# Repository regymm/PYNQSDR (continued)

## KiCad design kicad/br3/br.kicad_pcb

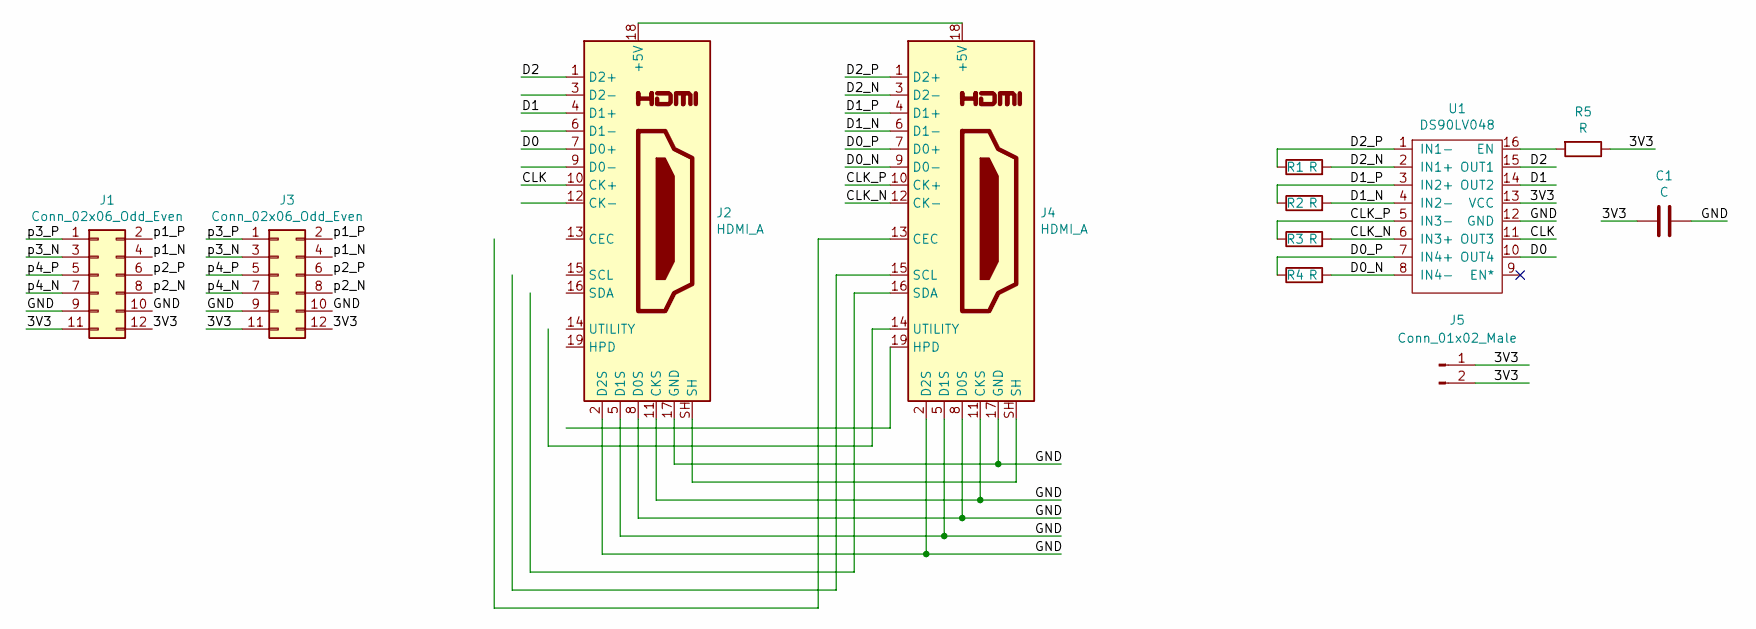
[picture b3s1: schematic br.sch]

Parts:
C1: C; C_0603_1608Metric_Pad1.08x0.95mm_HandSolder
J1, J3: Conn_02x06_Odd_Even; PinHeader_2x06_P2.54mm_Vertical
J2, J4: HDMI_A; HDMI_A_Kycon_KDMIX-SL1-NS-WS-B15_VerticalRightAngle
J5: Conn_01x02_Male; PinHeader_1x02_P2.54mm_Vertical
R1, R2, R3, R4, R5: R; R_0402_1005Metric_Pad0.72x0.64mm_HandSolder
U1: DS90LV048; SOIC-16_3.9x9.9mm_P1.27mm

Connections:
/3V3: C1.1, J1.11, J1.12, J3.11, J3.12, J5.1, J5.2, R5.1, U1.13 (VCC)
/CLK: J2.10 (CK+), U1.11 (OUT3)
/CLK_N: J4.12 (CK-), R3.2, U1.6 (IN3+)
/CLK_P: J4.10 (CK+), R3.1, U1.5 (IN3-)
/D0: J2.7 (D0+), U1.10 (OUT4)
/D0_N: J4.9 (D0-), R4.2, U1.8 (IN4-)
/D0_P: J4.7 (D0+), R4.1, U1.7 (IN4+)
/D1: J2.4 (D1+), U1.14 (OUT2)
/D1_N: J4.6 (D1-), R2.2, U1.4 (IN2-)
/D1_P: J4.4 (D1+), R2.1, U1.3 (IN2+)
/D2: J2.1 (D2+), U1.15 (OUT1)
/D2_N: J4.3 (D2-), R1.2, U1.2 (IN1+)
/D2_P: J4.1 (D2+), R1.1, U1.1 (IN1-)
/GND: C1.2, J1.9, J1.10, J2.2 (D2S), J2.5 (D1S), J2.8 (D0S), J2.11 (CKS), J2.17 (GND), J3.9, J3.10, J4.2 (D2S), J4.5 (D1S), J4.8 (D0S), J4.11 (CKS), J4.17 (GND), U1.12 (GND)
/p1_N: J1.4, J3.4
/p1_P: J1.2, J3.2
/p2_N: J1.8, J3.8
/p2_P: J1.6, J3.6
/p3_N: J1.3, J3.3
/p3_P: J1.1, J3.1
/p4_N: J1.7, J3.7
/p4_P: J1.5, J3.5
unnamed: J2.18 (+5V), J4.18 (+5V)
unnamed: J2.SH, J4.SH
unnamed: R5.2, U1.16 (EN)

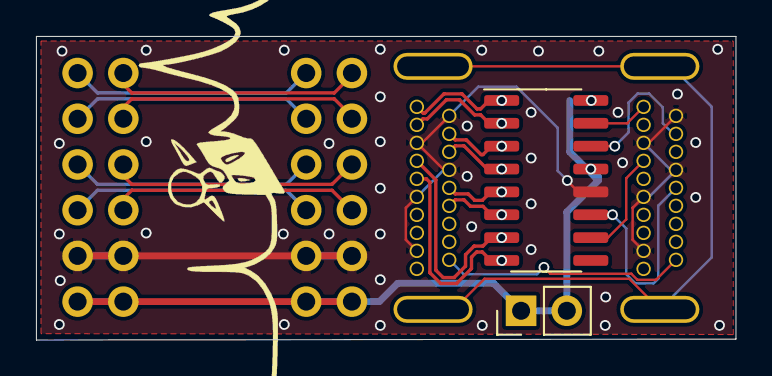
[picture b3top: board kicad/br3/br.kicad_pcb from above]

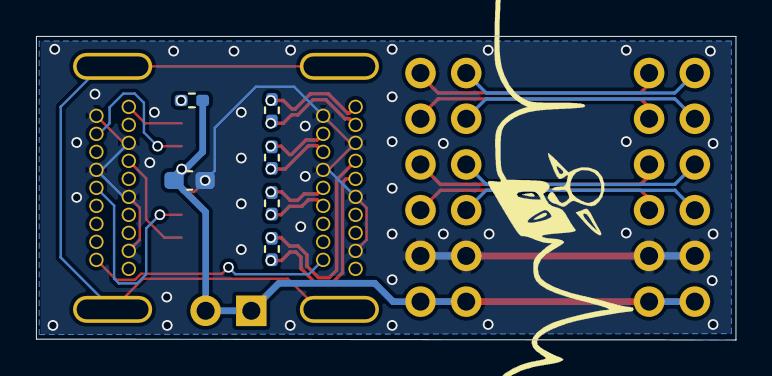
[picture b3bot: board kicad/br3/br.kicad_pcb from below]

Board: 2 copper layers, 38.9 x 16.9 mm, 12 parts (6 on the bottom side), 25 nets.

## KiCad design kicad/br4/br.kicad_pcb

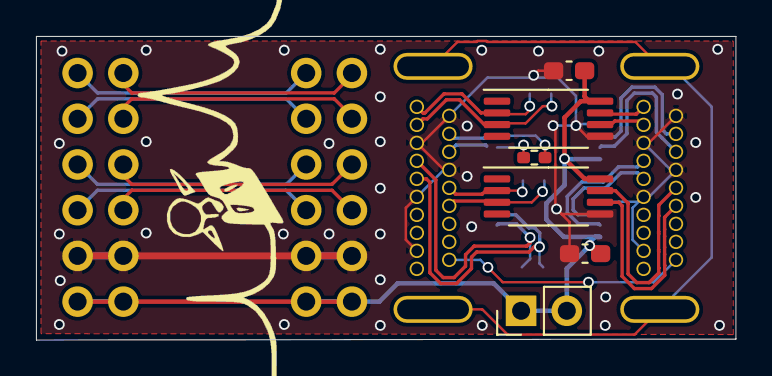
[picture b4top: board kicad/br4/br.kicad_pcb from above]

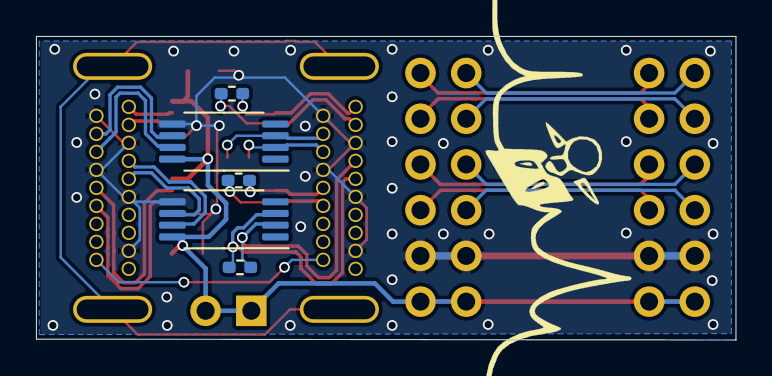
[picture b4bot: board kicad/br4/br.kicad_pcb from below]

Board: 2 copper layers, 38.9 x 16.9 mm, 15 parts (5 on the bottom side), 28 nets.

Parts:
C1, C2: C; C_0603_1608Metric_Pad1.08x0.95mm_HandSolder
J1, J3: Conn_02x06_Odd_Even; PinHeader_2x06_P2.54mm_Vertical
J2, J4: HDMI_A; HDMI_A_Kycon_KDMIX-SL1-NS-WS-B15_VerticalRightAngle
J5: Conn_01x02_Male; PinHeader_1x02_P2.54mm_Vertical
R1, R2, R3, R4: R; R_0402_1005Metric_Pad0.72x0.64mm_HandSolder
U1, U2, U3, U4: SN65CML100; TSSOP-8_4.4x3mm_P0.65mm

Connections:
/3V3: C1.1, C2.1, J1.11, J1.12, J3.11, J3.12, J5.1, J5.2, U1.8, U2.8, U3.8, U4.8
/CLK_N: J4.12, R3.2, U3.3
/CLK_P: J4.10, R3.1, U3.2
/CLK_TMDS_N: J2.12, U3.6
/CLK_TMDS_P: J2.10, U3.7
/D0_N: J4.9, R4.2, U4.3
/D0_P: J4.7, R4.1, U4.2
/D0_TMDS_N: J2.9, U4.6
/D0_TMDS_P: J2.7, U4.7
/D1_N: J4.6, R2.1, U2.2
/D1_P: J4.4, R2.2, U2.3
/D1_TMDS_N: J2.6, U2.7
/D1_TMDS_P: J2.4, U2.6
/D2_N: J4.3, R1.2, U1.3
/D2_P: J4.1, R1.1, U1.2
/D2_TMDS_N: J2.3, U1.6
/D2_TMDS_P: J2.1, U1.7
/GND: C1.2, C2.2, J1.9, J1.10, J2.2, J2.5, J2.8, J2.11, J2.17, J3.9, J3.10, J4.2, J4.5, J4.8, J4.11, J4.17, U1.5, U2.5, U3.5, U4.5
/p1_N: J1.4, J3.4
/p1_P: J1.2, J3.2
/p2_N: J1.8, J3.8
/p2_P: J1.6, J3.6
/p3_N: J1.3, J3.3
/p3_P: J1.1, J3.1
/p4_N: J1.7, J3.7
/p4_P: J1.5, J3.5
unnamed: J2.18, J4.18
unnamed: J2.SH, J4.SH

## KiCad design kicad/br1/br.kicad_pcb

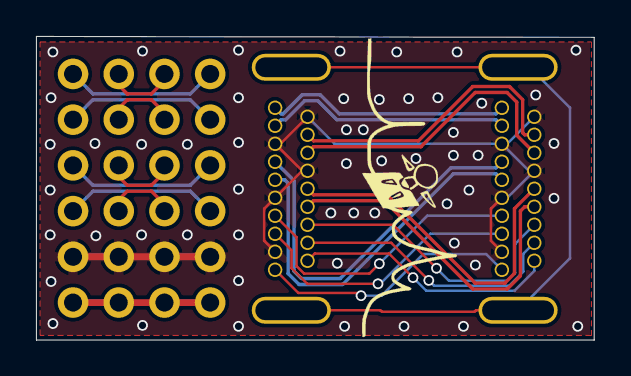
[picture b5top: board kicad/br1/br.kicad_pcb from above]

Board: 2 copper layers, 31.0 x 16.9 mm, 4 parts (0 on the bottom side), 25 nets.

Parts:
J1, J3: Conn_02x06_Odd_Even; PinHeader_2x06_P2.54mm_Vertical
J2, J4: HDMI_A; HDMI_A_Kycon_KDMIX-SL1-NS-WS-B15_VerticalRightAngle

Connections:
/3V3: J1.11, J1.12, J3.11, J3.12
/CLK_N: J2.12, J4.12
/CLK_P: J2.10, J4.10
/D0_N: J2.9, J4.9
/D0_P: J2.7, J4.7
/D1_N: J2.6, J4.6
/D1_P: J2.4, J4.4
/D2_N: J2.3, J4.3
/D2_P: J2.1, J4.1
/GND: J1.9, J1.10, J2.2, J2.5, J2.8, J2.11, J2.17, J3.9, J3.10, J4.2, J4.5, J4.8, J4.11, J4.17
/p1_N: J1.4, J3.3
/p1_P: J1.2, J3.1
/p2_N: J1.8, J3.7
/p2_P: J1.6, J3.5
/p3_N: J1.3, J3.4
/p3_P: J1.1, J3.2
/p4_N: J1.7, J3.8
/p4_P: J1.5, J3.6
unnamed: J2.13, J4.13
unnamed: J2.14, J4.14
unnamed: J2.15, J4.15
unnamed: J2.16, J4.16
unnamed: J2.18, J4.18
unnamed: J2.19, J4.19
unnamed: J2.SH, J4.SH

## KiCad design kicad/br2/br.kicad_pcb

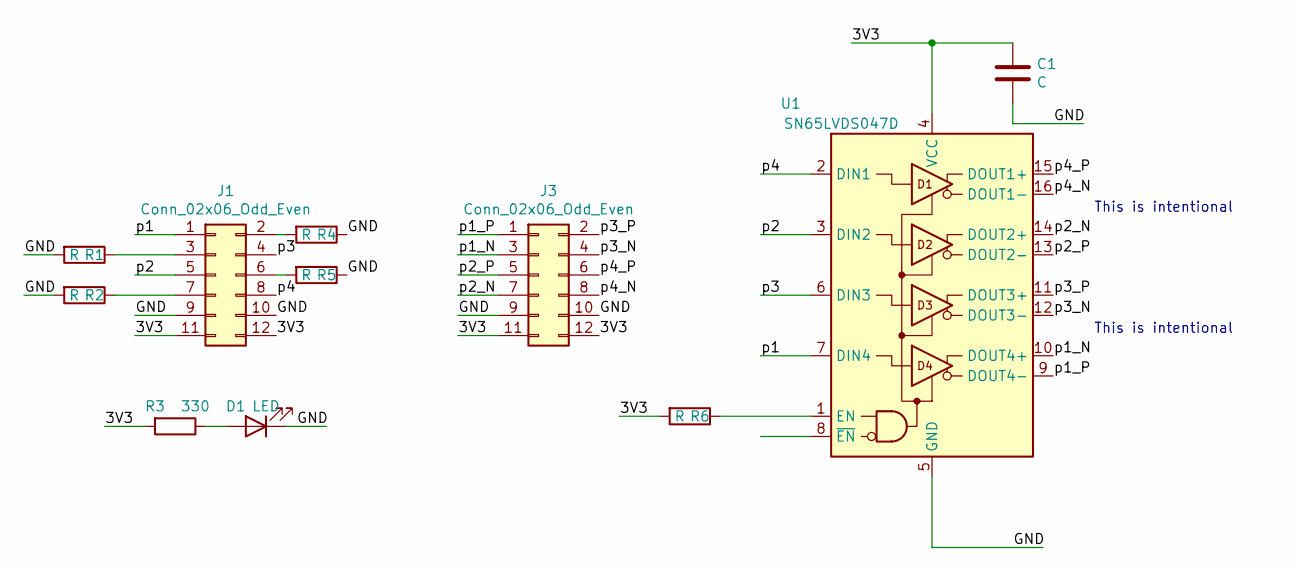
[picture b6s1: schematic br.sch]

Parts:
C1: C; C_0603_1608Metric_Pad1.08x0.95mm_HandSolder
D1: LED; LED_0603_1608Metric_Pad1.05x0.95mm_HandSolder
J1, J3: Conn_02x06_Odd_Even; PinHeader_2x06_P2.54mm_Vertical
R1, R2, R4, R5, R6: R; R_0402_1005Metric_Pad0.72x0.64mm_HandSolder
R3: 330; R_0603_1608Metric_Pad0.98x0.95mm_HandSolder
U1: SN65LVDS047D; SOIC-16_3.9x9.9mm_P1.27mm

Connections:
/3V3: C1.1, J1.11, J1.12, J3.11, J3.12, R3.2, R6.2, U1.4 (VCC)
/GND: C1.2, D1.1 (K), J1.9, J1.10, J3.9, J3.10, R1.2, R2.2, R4.1, R5.1, U1.5 (GND)
/p1: J1.1, U1.7 (DIN4)
/p1_N: J3.3, U1.10 (DOUT4+)
/p1_P: J3.1, U1.9 (DOUT4-)
/p2: J1.5, U1.3 (DIN2)
/p2_N: J3.7, U1.14 (DOUT2+)
/p2_P: J3.5, U1.13 (DOUT2-)
/p3: J1.4, U1.6 (DIN3)
/p3_N: J3.4, U1.12 (DOUT3-)
/p3_P: J3.2, U1.11 (DOUT3+)
/p4: J1.8, U1.2 (DIN1)
/p4_N: J3.8, U1.16 (DOUT1-)
/p4_P: J3.6, U1.15 (DOUT1+)
unnamed: D1.2 (A), R3.1
unnamed: J1.2, R4.2
unnamed: J1.3, R1.1
unnamed: J1.6, R5.2
unnamed: J1.7, R2.1
unnamed: R6.1, U1.1 (EN)

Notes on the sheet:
This is intentional

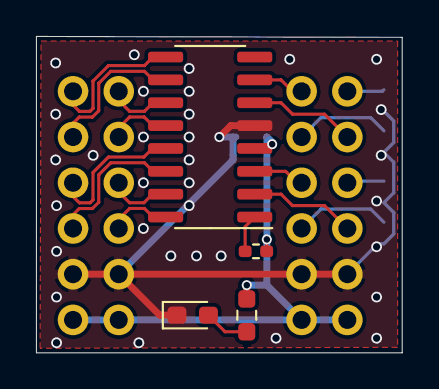
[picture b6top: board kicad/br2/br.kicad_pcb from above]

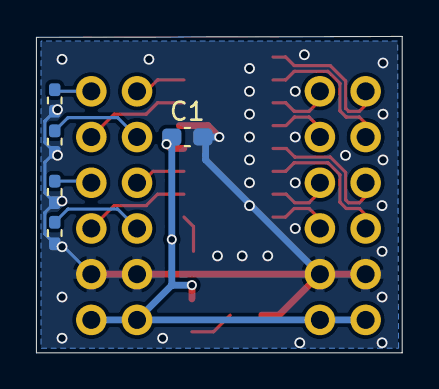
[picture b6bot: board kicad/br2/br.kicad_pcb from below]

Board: 2 copper layers, 20.3 x 17.6 mm, 11 parts (5 on the bottom side), 20 nets.

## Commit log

2021-12-03 Release
2021-12-04 Board files release
2021-12-20 V0.9 release and document update
2021-12-20 Pictures
2022-02-21 Clean up old files a littel bit
2022-02-21 v1.1 update
2022-02-21 Picture
2022-02-21 Forgot this
2022-03-04 Added quickstart
2022-10-28 V1.2 update
2022-11-03 Added first try of ebazsdr
2022-11-03 Added ebazsdr files
2022-11-07 Added store link
2022-11-19 Added pre-built images
2025-05-22 Update Quickstart.md Web Address
2025-07-07 Update README.md for Crowd Supply
